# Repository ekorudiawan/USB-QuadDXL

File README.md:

# USB-QuadDXL

USB-QuadDXL : USB to Dynamixel 4 Channel TTL port
This design was modified from bit-bots Quad DXL https://github.com/bit-bots/bitbots_quaddxl

Firmware will be updated later

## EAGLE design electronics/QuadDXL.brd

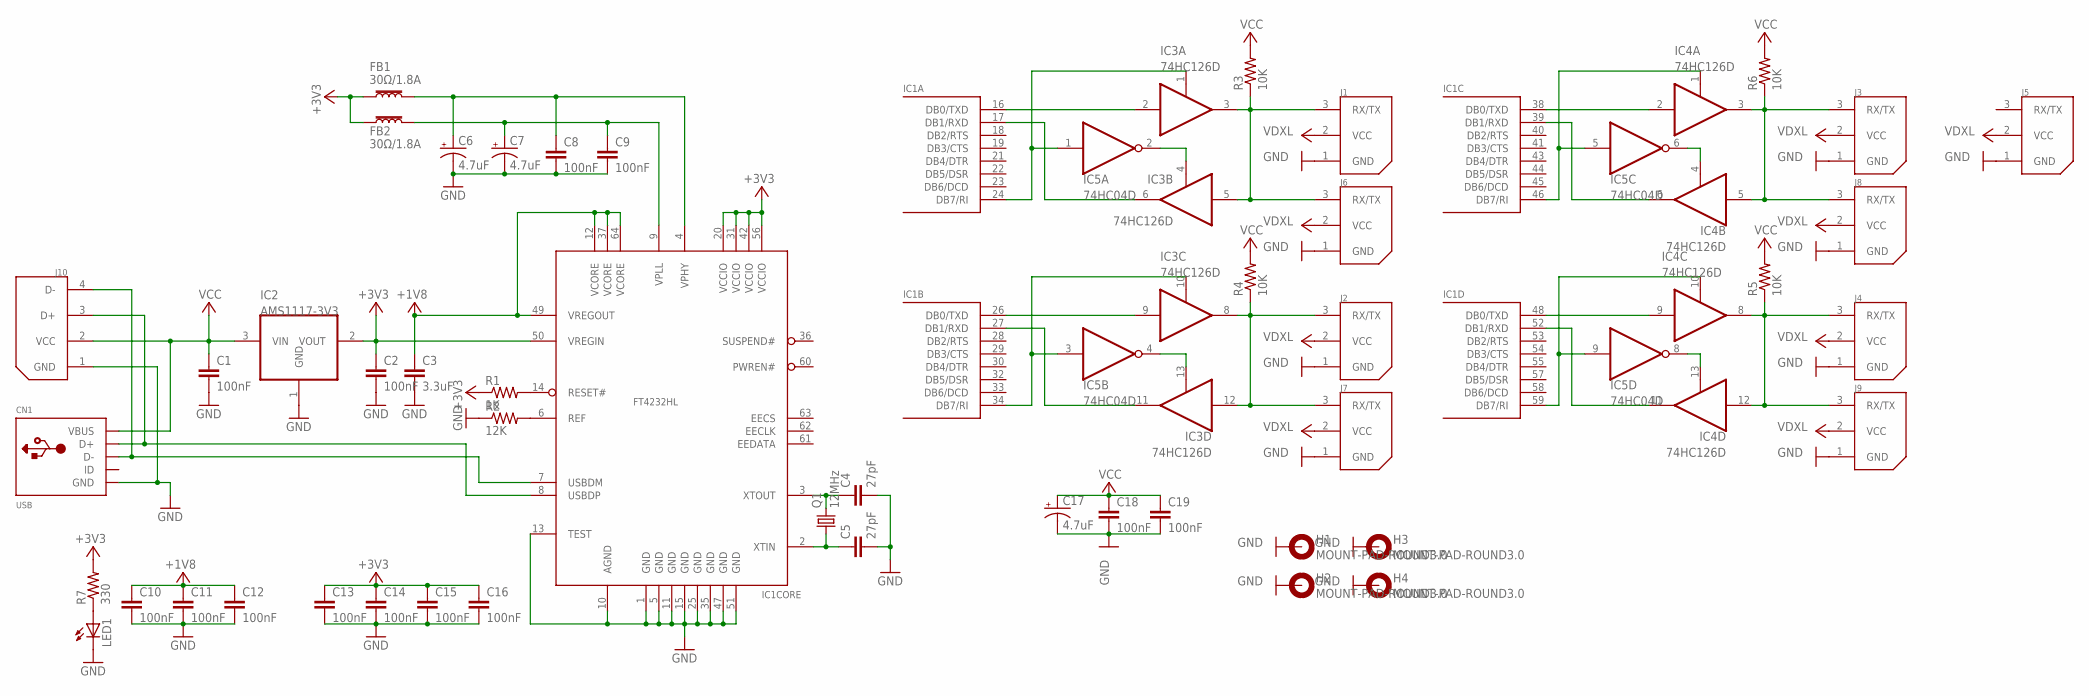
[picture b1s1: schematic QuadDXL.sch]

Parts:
C1, C2, C8, C9, C10, C11, C12, C13, C14, C15, C16, C18, C19: 100nF; C0603K
C3: 3.3uF; C0603K
C4, C5: 27pF; C0603K
C6, C7, C17: 4.7uF; CT3216
CN1: USB; USB-MINIB
FB1, FB2: 30Ω/1.8A; 0603
H1, H2, H3, H4: MOUNT-PAD-ROUND3.0; 3,0-PAD
IC1: FT4232HL; LQFP64
IC2: AMS1117-3V3; SOT223
IC3, IC4: 74HC126D; SO14
IC5: 74HC04D; SO14
J1, J2, J3, J4, J6, J7, J8, J9: 22-03-5035; 5267-3
J5: DXL_POWER; 5267-3
J10: USB; 5267-4
LED1: LEDCHIP-LED0603; CHIP-LED0603
Q1: 12MHz; HC49UP
R1: 1K; R0603
R2: 12K; R0603
R3, R4, R5, R6: 10K; R0603
R7: 330; R0603

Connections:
+1V8: C3.1, C10.1, C11.1, C12.1, IC1.12 (VCORE), IC1.37 (VCORE), IC1.49 (VREGOUT), IC1.64 (VCORE)
+3V3: C2.1, C13.1, C14.1, C15.1, C16.1, FB1.1, FB2.1, IC1.20 (VCCIO), IC1.31 (VCCIO), IC1.42 (VCCIO), IC1.50 (VREGIN), IC1.56 (VCCIO), IC2.2 (VOUT), R1.1, R7.2
GND: C1.2, C2.2, C3.2, C4.2, C5.2, C6.-, C7.-, C8.2, C9.2, C10.2, C11.2, C12.2, C13.2, C14.2, C15.2, C16.2, C17.-, C18.2, C19.2, CN1.GND, H1.B3,0, H2.B3,0, H3.B3,0, H4.B3,0, IC1.1 (GND), IC1.5 (GND), IC1.10 (AGND), IC1.11 (GND), IC1.13 (TEST), IC1.15 (GND), IC1.25 (GND), IC1.35 (GND), IC1.47 (GND), IC1.51 (GND), IC2.1 (GND), IC3.7 (GND), IC4.7 (GND), IC5.7 (GND), J1.1 (GND), J2.1 (GND), J3.1 (GND), J4.1 (GND), J5.1 (GND), J6.1 (GND), J7.1 (GND), J8.1 (GND), J9.1 (GND), J10.1 (GND), LED1.C, R2.1
unnamed: CN1.D+, IC1.8 (USBDP), J10.3 (D+)
unnamed: CN1.D-, IC1.7 (USBDM), J10.4 (D-)
unnamed: LED1.A, R7.1
unnamed: IC1.14 (RESET#), R1.2
unnamed: IC1.6 (REF), R2.2
unnamed: C4.1, IC1.3 (XTOUT), Q1.2
unnamed: C5.1, IC1.2 (XTIN), Q1.1
unnamed: C6.+, C8.1, FB1.2, IC1.4 (VPHY)
unnamed: C7.+, C9.1, FB2.2, IC1.9 (VPLL)
unnamed: IC1.16 (DB0/TXD), IC3.2 (I)
unnamed: IC1.17 (DB1/RXD), IC3.6 (O)
unnamed: IC1.24 (DB7/RI), IC3.1 (OE), IC5.1 (I)
unnamed: IC3.4 (OE), IC5.2 (O)
unnamed: IC3.3 (O), IC3.5 (I), J1.3 (RX/TX), J6.3 (RX/TX), R3.1
unnamed: IC1.26 (DB0/TXD), IC3.9 (I)
unnamed: IC1.27 (DB1/RXD), IC3.11 (O)
unnamed: IC1.34 (DB7/RI), IC3.10 (OE), IC5.3 (I)
unnamed: IC3.13 (OE), IC5.4 (O)
unnamed: IC3.8 (O), IC3.12 (I), J2.3 (RX/TX), J7.3 (RX/TX), R4.1
unnamed: IC1.38 (DB0/TXD), IC4.2 (I)
unnamed: IC1.39 (DB1/RXD), IC4.6 (O)
unnamed: IC4.4 (OE), IC5.6 (O)
unnamed: IC1.46 (DB7/RI), IC4.1 (OE), IC5.5 (I)
unnamed: IC1.48 (DB0/TXD), IC4.9 (I)
unnamed: IC1.59 (DB7/RI), IC4.10 (OE), IC5.9 (I)
unnamed: IC4.13 (OE), IC5.8 (O)
unnamed: IC1.52 (DB1/RXD), IC4.11 (O)
unnamed: IC4.3 (O), IC4.5 (I), J3.3 (RX/TX), J8.3 (RX/TX), R6.1
unnamed: IC4.8 (O), IC4.12 (I), J4.3 (RX/TX), J9.3 (RX/TX), R5.1
VCC: C1.1, C17.+, C18.1, C19.1, CN1.VBUS, IC2.3 (VIN), IC3.14 (VCC), IC4.14 (VCC), IC5.14 (VCC), J10.2 (VCC), R3.2, R4.2, R5.2, R6.2
VDXL: J1.2 (VCC), J2.2 (VCC), J3.2 (VCC), J4.2 (VCC), J5.2 (VCC), J6.2 (VCC), J7.2 (VCC), J8.2 (VCC), J9.2 (VCC)

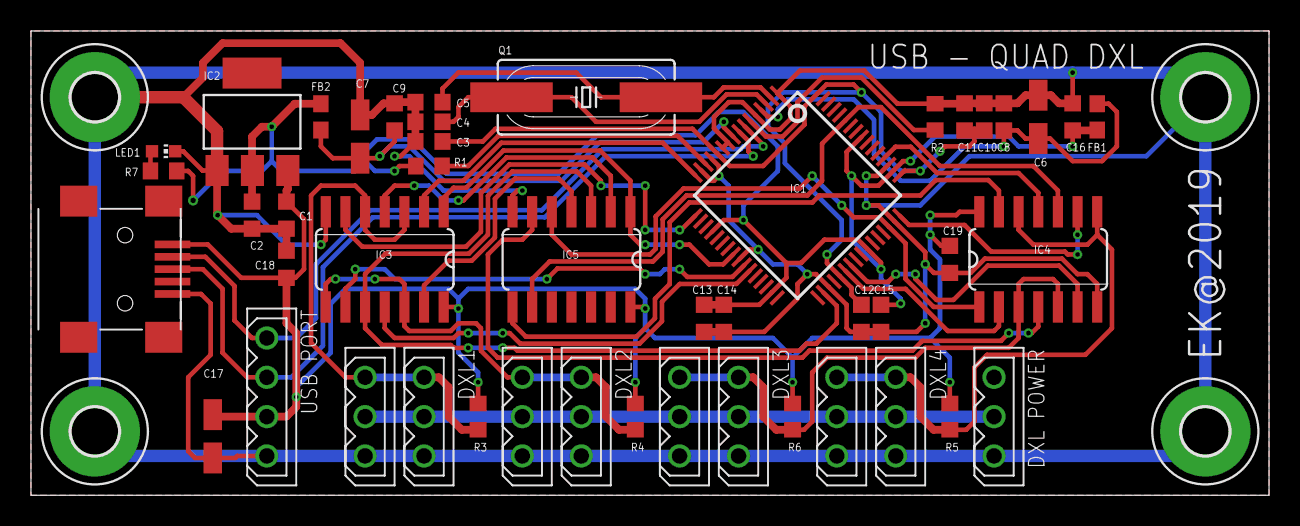
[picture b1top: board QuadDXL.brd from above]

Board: 2 copper layers, 80.0 x 30.0 mm, 50 parts (0 on the bottom side), 34 nets.

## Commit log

2019-10-08 Added design files
2019-10-08 move to electronics folder
2019-10-08 update documentation

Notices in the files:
parts and their libraries:
SparkFun-Coils: Licensing: Creative Commons ShareAlike 4.0 International - https://creativecommons.org/licenses/by-sa/4.0
